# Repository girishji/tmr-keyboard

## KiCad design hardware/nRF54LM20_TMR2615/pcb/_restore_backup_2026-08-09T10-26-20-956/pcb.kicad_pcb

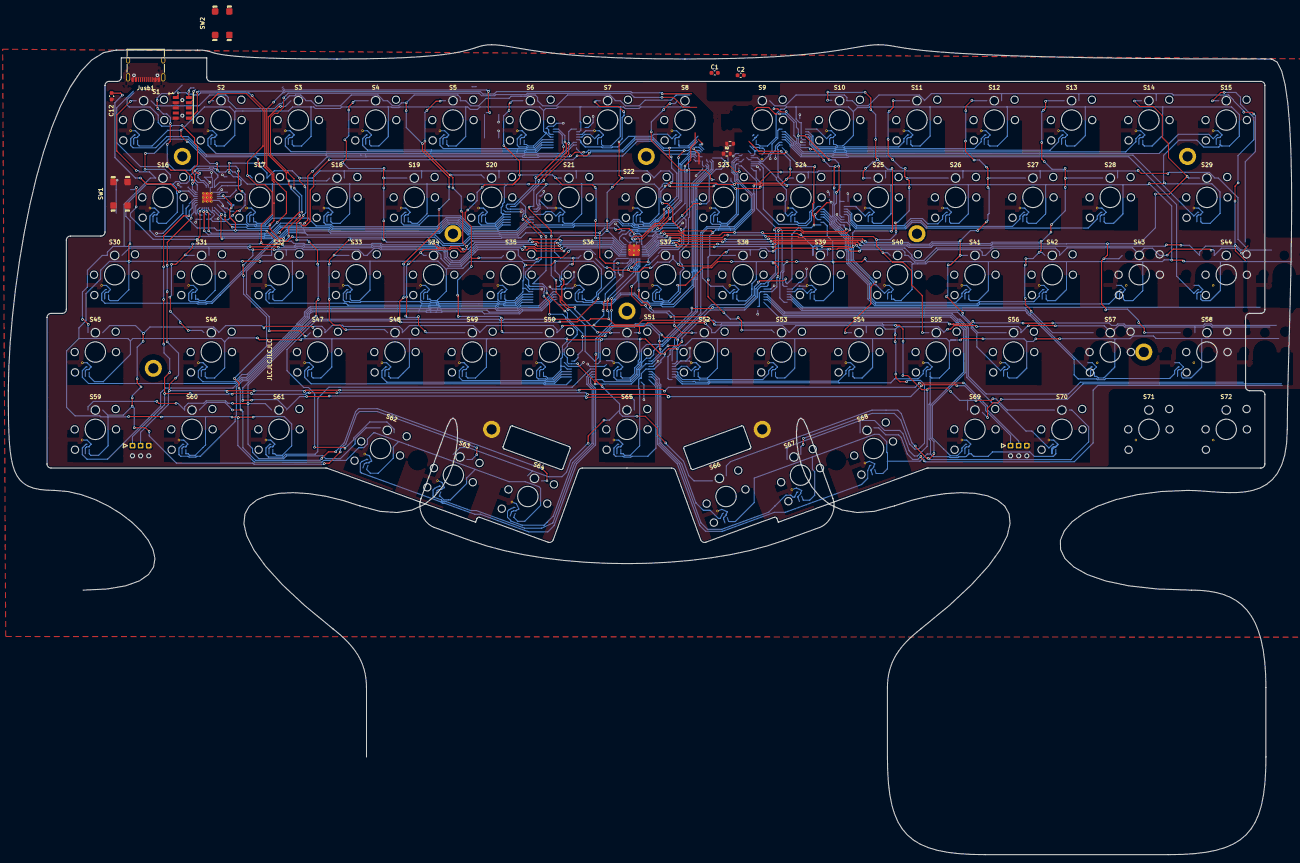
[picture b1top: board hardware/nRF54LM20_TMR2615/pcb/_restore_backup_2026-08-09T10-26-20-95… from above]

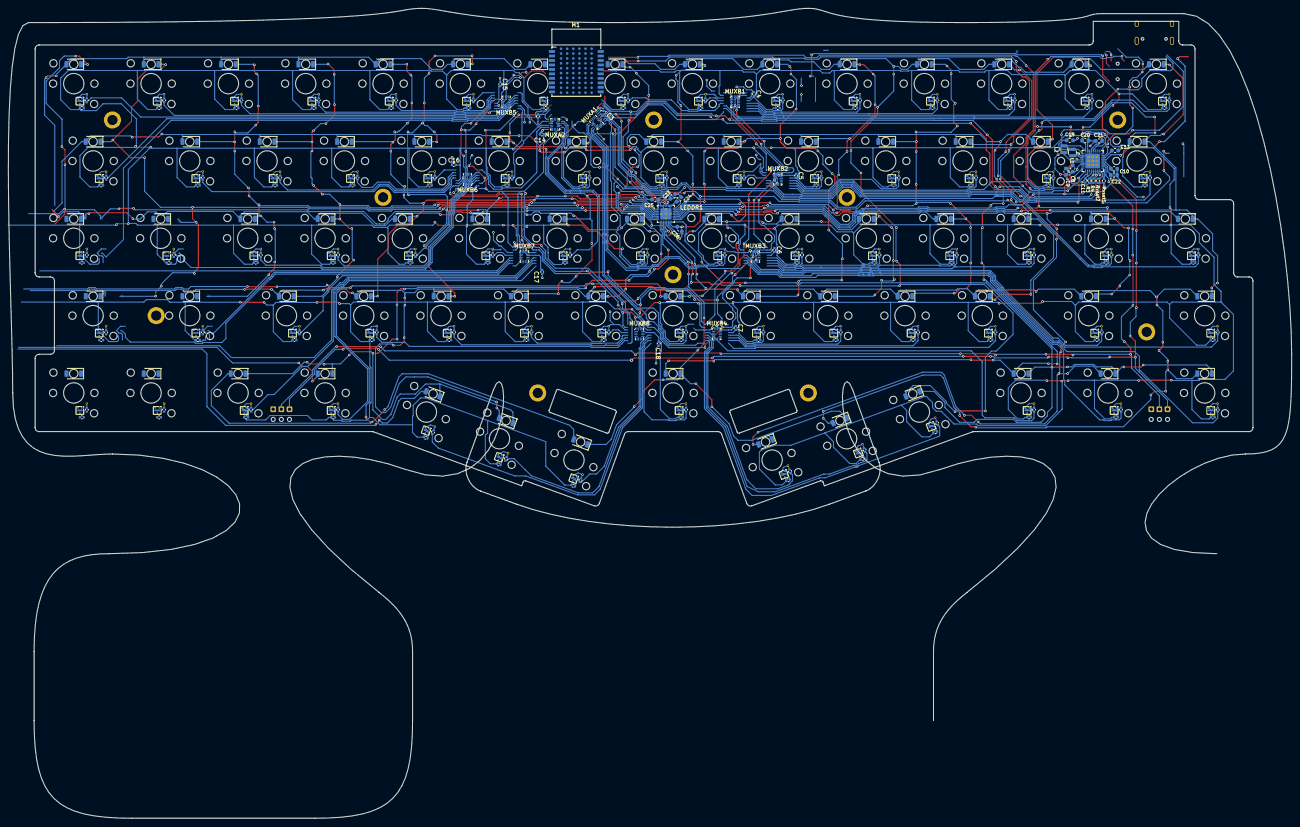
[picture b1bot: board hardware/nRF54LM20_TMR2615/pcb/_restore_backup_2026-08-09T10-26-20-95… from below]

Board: 2 copper layers, 315.3 x 199.0 mm, 426 parts (330 on the bottom side), 144 nets.

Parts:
BAT1, BAT2: PCB_Wire_Solder_3p_Connector
C1, C2, C8, C9, C10, C19, C20: 10uF; C_0603_1608Metric
C3, C4, C5, C6, C7, C14, C15, C16, C17, C18: .1uF; C_0402_1005Metric
C11: 0.1uF; C_0402_1005Metric
C12, C13, C24, C25, C26: 1uF; C_0603_1608Metric
C21, C22: 2.2uF; C_0603_1608Metric
C23: 1nF; C_0603_1608Metric
Cvcc1, Cvcc2, Cvcc3, Cvcc4, Cvcc5, Cvcc6, Cvcc7, Cvcc8, Cvcc9, Cvcc10, Cvcc11, Cvcc12, Cvcc13, Cvcc14, Cvcc15, Cvcc16, Cvcc17, Cvcc18, Cvcc19, Cvcc20, Cvcc21, Cvcc22, Cvcc23, Cvcc24, Cvcc25, Cvcc26, Cvcc27, Cvcc28, Cvcc29, Cvcc30, Cvcc31, Cvcc32, Cvcc33, Cvcc34, Cvcc35, Cvcc36, Cvcc37, Cvcc38, Cvcc39, Cvcc40, Cvcc41, Cvcc42, Cvcc43, Cvcc44, Cvcc45, Cvcc46, Cvcc47, Cvcc48, Cvcc49, Cvcc50, Cvcc51, Cvcc52, Cvcc53, Cvcc54, Cvcc55, Cvcc56, Cvcc57, Cvcc58, Cvcc59, Cvcc60, Cvcc61, Cvcc62, Cvcc63, Cvcc64, Cvcc65, Cvcc66, Cvcc67, Cvcc68, Cvcc69, Cvcc70, Cvcc71, Cvcc72: 0.1uF; C_0402_1005Metric_Cvcc
Cvout1, Cvout2, Cvout3, Cvout4, Cvout5, Cvout6, Cvout7, Cvout8, Cvout9, Cvout10, Cvout11, Cvout12, Cvout13, Cvout14, Cvout15, Cvout16, Cvout17, Cvout18, Cvout19, Cvout20, Cvout21, Cvout22, Cvout23, Cvout24, Cvout25, Cvout26, Cvout27, Cvout28, Cvout29, Cvout30, Cvout31, Cvout32, Cvout33, Cvout34, Cvout35, Cvout36, Cvout37, Cvout38, Cvout39, Cvout40, Cvout41, Cvout42, Cvout43, Cvout44, Cvout45, Cvout46, Cvout47, Cvout48, Cvout49, Cvout50, Cvout51, Cvout52, Cvout53, Cvout54, Cvout55, Cvout56, Cvout57, Cvout58, Cvout59, Cvout60, Cvout61, Cvout62, Cvout63, Cvout64, Cvout65, Cvout66, Cvout67, Cvout68, Cvout69, Cvout70, Cvout71, Cvout72: 0.1nF; C_0402_1005Metric_Cvout
D1, D2, D3, D4, D5, D6, D7, D8, D9, D10, D11, D12, D13, D14, D15, D16, D17, D18, D19, D20, D21, D22, D23, D24, D25, D26, D27, D28, D29, D30, D31, D32, D33, D34, D35, D36, D37, D38, D39, D40, D41, D42, D43, D44, D45, D46, D47, D48, D49, D50, D51, D52, D53, D54, D55, D56, D57, D58, D59, D60, D61, D62, D63, D64, D65, D66, D67, D68, D69, D70, D71, D72: Green LED; LED_1206_3216Metric_ReverseMount_Hole2.1mm
Hs1, Hs2, Hs3, Hs4, Hs5, Hs6, Hs7, Hs8, Hs9, Hs10: SMTSO1.6; SMTSO_M1.6
JLC1: JLC_Order_Num
JTAG1: Conn_ARM_JTAG_SWD_10; SAMTEC-CLP-105-02-X-D-A
Jusb1: USB_TYPE_C_Receptacle_16P; USB_C_Receptacle_XKB_U262-16XN-4BVC11
L1, L2: 2.2uH; L_Samsung_CIGT201610EH2R2MNE
LEDDR1: LP5864; LP5864-VQFN-32-1EP_4x4mm_P0.4mm_EP2.8x2.8mm_ThermalVias
M1: Minew_ME54BS13_V1.0; Minew_ME54BS13
MUXA1, MUXA2: TMUX1574RSV; UQFN-16_1.8x2.6mm_P0.4mm
MUXB1, MUXB2, MUXB3, MUXB4, MUXB5, MUXB6, MUXB7, MUXB8: TMUX1208RSV; UQFN-16_1.8x2.6mm_P0.4mm
PMIC1: nPM1300-QEXX; QFN-32-1EP_5x5mm_P0.5mm_EP3.6x3.6mm_ThermalVias
R1, R2: 27R; R_0603_1608Metric
R3, R4: 10k; R_0402_1005Metric
Rvset1: 150k; R_0402_1005Metric
Rvset2: 4.7k; R_0402_1005Metric
S1, S2, S3, S4, S5, S6, S7, S8, S9, S10, S11, S12, S13, S14, S15, S16, S17, S18, S19, S20, S21, S22, S23, S24, S25, S26, S27, S28, S29, S30, S31, S32, S33, S34, S35, S36, S37, S38, S39, S40, S41, S42, S43, S44, S45, S46, S47, S48, S49, S50, S51, S52, S53, S54, S55, S56, S57, S58, S59, S60, S61, S62, S63, S64, S65, S66, S67, S68, S69, S70, S71, S72: Switch; Kailh_gateron_sw_lowpro
SW1, SW2: SW_DIP_x01; Aliexpress_SW_TACT_4x4x1.5mm
Stb1, Stb2: TMR_switch_stab_2.0u; Stabilizer_Lowpro_2U
TMR1, TMR2, TMR3, TMR4, TMR5, TMR6, TMR7, TMR8, TMR9, TMR10, TMR11, TMR12, TMR13, TMR14, TMR15, TMR16, TMR17, TMR18, TMR19, TMR20, TMR21, TMR22, TMR23, TMR24, TMR25, TMR26, TMR27, TMR28, TMR29, TMR30, TMR31, TMR32, TMR33, TMR34, TMR35, TMR36, TMR37, TMR38, TMR39, TMR40, TMR41, TMR42, TMR43, TMR44, TMR45, TMR46, TMR47, TMR48, TMR49, TMR50, TMR51, TMR52, TMR53, TMR54, TMR55, TMR56, TMR57, TMR58, TMR59, TMR60, TMR61, TMR62, TMR63, TMR64, TMR65, TMR66, TMR67, TMR68, TMR69, TMR70, TMR71, TMR72: TMR2615; TMR2615-DFN-3L-1.6x1.6

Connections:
/AIN0: M1.A7 (P1.00/AIN0), MUXA1.2 (D1)
/AIN1: M1.B7 (P1.31/AIN1), MUXA1.5 (D2)
/AIN2: M1.A9 (P1.30/AIN2), MUXA1.7 (D3)
/AIN3: M1.B9 (P1.29/AIN3), MUXA1.10 (D4)
/AIN4: M1.A6 (P1.06/AIN4), MUXA2.7 (D3)
/AIN5: M1.C7 (P1.05/AIN5), MUXA2.10 (D4)
/AIN6: M1.A8 (P1.04/AIN6), MUXA2.2 (D1)
/AIN7: M1.B8 (P1.03/AIN7), MUXA2.5 (D2)
/ANA_01: Cvout1.1, MUXB1.5 (S4), TMR1.1 (V_{OUT})
/ANA_02: Cvout2.1, MUXB1.4 (S3), TMR2.1 (V_{OUT})
/ANA_03: Cvout3.1, MUXB1.7 (S8), TMR3.1 (V_{OUT})
/ANA_04: Cvout4.1, MUXB1.8 (S7), TMR4.1 (V_{OUT})
/ANA_05: Cvout5.1, MUXB1.9 (S6), TMR5.1 (V_{OUT})
/ANA_06: Cvout6.1, MUXB1.10 (S5), TMR6.1 (V_{OUT})
/ANA_07: Cvout7.1, MUXB1.2 (S1), TMR7.1 (V_{OUT})
/ANA_08: Cvout8.1, MUXB1.3 (S2), TMR8.1 (V_{OUT})
/ANA_09: Cvout9.1, MUXA2.8 (S3B), TMR9.1 (V_{OUT})
/ANA_10: Cvout10.1, MUXB5.7 (S8), TMR10.1 (V_{OUT})
/ANA_11: Cvout11.1, MUXB5.8 (S7), TMR11.1 (V_{OUT})
/ANA_12: Cvout12.1, MUXB5.9 (S6), TMR12.1 (V_{OUT})
/ANA_13: Cvout13.1, MUXB5.10 (S5), TMR13.1 (V_{OUT})
/ANA_14: Cvout14.1, MUXB5.5 (S4), TMR14.1 (V_{OUT})
/ANA_15: Cvout15.1, MUXB5.4 (S3), TMR15.1 (V_{OUT})
/ANA_16: Cvout16.1, MUXB2.3 (S2), TMR16.1 (V_{OUT})
/ANA_17: Cvout17.1, MUXB2.7 (S8), TMR17.1 (V_{OUT})
/ANA_18: Cvout18.1, MUXB2.8 (S7), TMR18.1 (V_{OUT})
/ANA_19: Cvout19.1, MUXB2.9 (S6), TMR19.1 (V_{OUT})
/ANA_20: Cvout20.1, MUXB2.10 (S5), TMR20.1 (V_{OUT})
/ANA_21: Cvout21.1, MUXB2.2 (S1), TMR21.1 (V_{OUT})
/ANA_22: Cvout22.1, MUXA1.11 (S4B), TMR22.1 (V_{OUT})
/ANA_23: Cvout23.1, MUXA2.4 (S2B), TMR23.1 (V_{OUT})
/ANA_24: Cvout24.1, MUXA2.11 (S4B), TMR24.1 (V_{OUT})
/ANA_25: Cvout25.1, MUXB6.7 (S8), TMR25.1 (V_{OUT})
/ANA_26: Cvout26.1, MUXB6.8 (S7), TMR26.1 (V_{OUT})
/ANA_27: Cvout27.1, MUXB6.9 (S6), TMR27.1 (V_{OUT})
/ANA_28: Cvout28.1, MUXB6.10 (S5), TMR28.1 (V_{OUT})
/ANA_29: Cvout29.1, MUXB5.3 (S2), TMR29.1 (V_{OUT})
/ANA_30: Cvout30.1, MUXB2.5 (S4), TMR30.1 (V_{OUT})
/ANA_31: Cvout31.1, MUXB2.4 (S3), TMR31.1 (V_{OUT})
/ANA_32: Cvout32.1, MUXB3.7 (S8), TMR32.1 (V_{OUT})
/ANA_33: Cvout33.1, MUXB3.8 (S7), TMR33.1 (V_{OUT})
/ANA_34: Cvout34.1, MUXB3.9 (S6), TMR34.1 (V_{OUT})
/ANA_35: Cvout35.1, MUXB3.10 (S5), TMR35.1 (V_{OUT})
/ANA_36: Cvout36.1, MUXA1.4 (S2B), TMR36.1 (V_{OUT})
/ANA_37: Cvout37.1, MUXA1.8 (S3B), TMR37.1 (V_{OUT})
/ANA_38: Cvout38.1, MUXA2.1 (S1B), TMR38.1 (V_{OUT})
/ANA_39: Cvout39.1, MUXB7.2 (S1), TMR39.1 (V_{OUT})
/ANA_40: Cvout40.1, MUXB6.5 (S4), TMR40.1 (V_{OUT})
/ANA_41: Cvout41.1, MUXB6.4 (S3), TMR41.1 (V_{OUT})
/ANA_42: Cvout42.1, MUXB6.3 (S2), TMR42.1 (V_{OUT})
/ANA_43: Cvout43.1, MUXB6.2 (S1), TMR43.1 (V_{OUT})
/ANA_44: Cvout44.1, MUXB5.2 (S1), TMR44.1 (V_{OUT})
/ANA_45: Cvout45.1, MUXB3.3 (S2), TMR45.1 (V_{OUT})
/ANA_46: Cvout46.1, MUXB3.2 (S1), TMR46.1 (V_{OUT})
/ANA_47: Cvout47.1, MUXB4.7 (S8), TMR47.1 (V_{OUT})
/ANA_48: Cvout48.1, MUXB4.8 (S7), TMR48.1 (V_{OUT})
/ANA_49: Cvout49.1, MUXB4.9 (S6), TMR49.1 (V_{OUT})
/ANA_50: Cvout50.1, MUXB4.10 (S5), TMR50.1 (V_{OUT})
/ANA_51: Cvout51.1, MUXA1.1 (S1B), TMR51.1 (V_{OUT})
/ANA_52: Cvout52.1, MUXB8.2 (S1), TMR52.1 (V_{OUT})
/ANA_53: Cvout53.1, MUXB8.3 (S2), TMR53.1 (V_{OUT})
/ANA_54: Cvout54.1, MUXB8.4 (S3), TMR54.1 (V_{OUT})
/ANA_55: Cvout55.1, MUXB8.5 (S4), TMR55.1 (V_{OUT})
/ANA_56: Cvout56.1, MUXB7.10 (S5), TMR56.1 (V_{OUT})
/ANA_57: Cvout57.1, MUXB7.4 (S3), TMR57.1 (V_{OUT})
/ANA_58: Cvout58.1, MUXB7.5 (S4), TMR58.1 (V_{OUT})
/ANA_59: Cvout59.1, MUXB3.4 (S3), TMR59.1 (V_{OUT})
/ANA_60: Cvout60.1, MUXB3.5 (S4), TMR60.1 (V_{OUT})
/ANA_61: Cvout61.1, MUXB4.2 (S1), TMR61.1 (V_{OUT})
/ANA_62: Cvout62.1, MUXB4.5 (S4), TMR62.1 (V_{OUT})
/ANA_63: Cvout63.1, MUXB4.4 (S3), TMR63.1 (V_{OUT})
/ANA_64: Cvout64.1, MUXB4.3 (S2), TMR64.1 (V_{OUT})
/ANA_65: Cvout65.1, MUXB8.7 (S8), TMR65.1 (V_{OUT})
/ANA_66: Cvout66.1, MUXB8.10 (S5), TMR66.1 (V_{OUT})
/ANA_67: Cvout67.1, MUXB8.9 (S6), TMR67.1 (V_{OUT})
/ANA_68: Cvout68.1, MUXB8.8 (S7), TMR68.1 (V_{OUT})
/ANA_69: Cvout69.1, MUXB7.7 (S8), TMR69.1 (V_{OUT})
/ANA_70: Cvout70.1, MUXB7.8 (S7), TMR70.1 (V_{OUT})
/ANA_71: Cvout71.1, MUXB7.9 (S6), TMR71.1 (V_{OUT})
/ANA_72: Cvout72.1, MUXB7.3 (S2), TMR72.1 (V_{OUT})
/CS0: D9.1 (K), D24.1 (K), D38.1 (K), D53.1 (K), LEDDR1.2 (CS0)
/CS1: D10.1 (K), D25.1 (K), D39.1 (K), D54.1 (K), LEDDR1.3 (CS1)
/CS2: D11.1 (K), D26.1 (K), D40.1 (K), D55.1 (K), LEDDR1.4 (CS2)
/CS3: D12.1 (K), D27.1 (K), D41.1 (K), D56.1 (K), LEDDR1.5 (CS3)
/CS4: D13.1 (K), D28.1 (K), D42.1 (K), D57.1 (K), LEDDR1.6 (CS4)
/CS5: D14.1 (K), D29.1 (K), D43.1 (K), D58.1 (K), LEDDR1.7 (CS5)
/CS6: D15.1 (K), D44.1 (K), D71.1 (K), D72.1 (K), LEDDR1.8 (CS6)
/CS7: D67.1 (K), D68.1 (K), D69.1 (K), D70.1 (K), LEDDR1.9 (CS7)
/CS8: D63.1 (K), D64.1 (K), D65.1 (K), D66.1 (K), LEDDR1.10 (CS8)
/CS9: D59.1 (K), D60.1 (K), D61.1 (K), D62.1 (K), LEDDR1.16 (CS9)
/CS10: D1.1 (K), D16.1 (K), D30.1 (K), D45.1 (K), LEDDR1.17 (CS10)
/CS11: D2.1 (K), D17.1 (K), D31.1 (K), D46.1 (K), LEDDR1.18 (CS11)
/CS12: D3.1 (K), D18.1 (K), D32.1 (K), D47.1 (K), LEDDR1.19 (CS12)
/CS13: D4.1 (K), D19.1 (K), D33.1 (K), D48.1 (K), LEDDR1.20 (CS13)
/CS14: D5.1 (K), D20.1 (K), D34.1 (K), D49.1 (K), LEDDR1.21 (CS14)
/CS15: D6.1 (K), D21.1 (K), D35.1 (K), D50.1 (K), LEDDR1.22 (CS15)
/CS16: D7.1 (K), D22.1 (K), D36.1 (K), D51.1 (K), LEDDR1.23 (CS16)
/CS17: D8.1 (K), D23.1 (K), D37.1 (K), D52.1 (K), LEDDR1.24 (CS17)
/GPIO_X: M1.13 (P1.23), PMIC1.10 (GPIO3)
/INT: M1.12 (P1.26), PMIC1.8 (GPIO1)
/LED_DR_EN: C23.1, LEDDR1.32 (VIO_EN), M1.F3 (P1.13)
/LOADSW_CTRL: M1.14 (P1.19), PMIC1.9 (GPIO2)
/MUXA_SEL: M1.15 (P1.18), MUXA1.15 (SEL), MUXA2.15 (SEL)
/MUXB_SEL_0: M1.17 (P1.16), MUXB1.15 (A0), MUXB2.15 (A0), MUXB3.15 (A0), MUXB4.15 (A0), MUXB5.15 (A0), MUXB6.15 (A0), MUXB7.15 (A0), MUXB8.15 (A0)
/MUXB_SEL_1: M1.16 (P1.17), MUXB1.14 (A1), MUXB2.14 (A1), MUXB3.14 (A1), MUXB4.14 (A1), MUXB5.14 (A1), MUXB6.14 (A1), MUXB7.14 (A1), MUXB8.14 (A1)
/MUXB_SEL_2: M1.18 (P1.15), MUXB1.13 (A2), MUXB2.13 (A2), MUXB3.13 (A2), MUXB4.13 (A2), MUXB5.13 (A2), MUXB6.13 (A2), MUXB7.13 (A2), MUXB8.13 (A2)
/MUX_B_1: MUXA1.12 (S4A), MUXB1.6 (D)
/MUX_B_2: MUXA1.9 (S3A), MUXB2.6 (D)
/MUX_B_3: MUXA1.3 (S2A), MUXB3.6 (D)
/MUX_B_4: MUXA1.16 (S1A), MUXB4.6 (D)
/MUX_B_5: MUXA2.9 (S3A), MUXB5.6 (D)
/MUX_B_6: MUXA2.12 (S4A), MUXB6.6 (D)
/MUX_B_7: MUXA2.16 (S1A), MUXB7.6 (D)
/MUX_B_8: MUXA2.3 (S2A), MUXB8.6 (D)
/NRESET: JTAG1.10 (~RESET), M1.4 (nRESET), SW1.2
/SCL: LEDDR1.28 (SCL_SCLK), M1.F4 (P1.12), PMIC1.14 (SCL), R3.2
/SDA: LEDDR1.29 (SDA_MOSI), M1.F5 (P1.11), PMIC1.13 (SDA), R4.2
/SW0: D1.2 (A), D2.2 (A), D3.2 (A), D4.2 (A), D5.2 (A), D6.2 (A), D7.2 (A), D8.2 (A), D9.2 (A), D10.2 (A), D11.2 (A), D12.2 (A), D13.2 (A), D14.2 (A), D15.2 (A), D62.2 (A), D66.2 (A), D70.2 (A), LEDDR1.11 (SW0)
/SW1: D16.2 (A), D17.2 (A), D18.2 (A), D19.2 (A), D20.2 (A), D21.2 (A), D22.2 (A), D23.2 (A), D24.2 (A), D25.2 (A), D26.2 (A), D27.2 (A), D28.2 (A), D29.2 (A), D61.2 (A), D65.2 (A), D69.2 (A), D72.2 (A), LEDDR1.12 (SW1)
/SW2: D30.2 (A), D31.2 (A), D32.2 (A), D33.2 (A), D34.2 (A), D35.2 (A), D36.2 (A), D37.2 (A), D38.2 (A), D39.2 (A), D40.2 (A), D41.2 (A), D42.2 (A), D43.2 (A), D44.2 (A), D60.2 (A), D64.2 (A), D68.2 (A), LEDDR1.13 (SW2)
/SW3: D45.2 (A), D46.2 (A), D47.2 (A), D48.2 (A), D49.2 (A), D50.2 (A), D51.2 (A), D52.2 (A), D53.2 (A), D54.2 (A), D55.2 (A), D56.2 (A), D57.2 (A), D58.2 (A), D59.2 (A), D63.2 (A), D67.2 (A), D71.2 (A), LEDDR1.14 (SW3)
/SWDCLK: JTAG1.4 (SWCLK/TCK), M1.6 (SWDCLK)
/SWDIO: JTAG1.2 (SWDIO/TMS), M1.5 (SWDIO)
/USB_D+: Jusb1.A6 (D1+), Jusb1.B6 (D2+), R2.1
/USB_D-: Jusb1.A7 (D1-), Jusb1.B7 (D2-), R1.1
/VBAT: BAT1.1 (VBAT), BAT2.1 (VBAT), C22.1, PMIC1.19 (VBAT)
/VBUSOUT: C2.1, C13.1, M1.9 (VBUS), PMIC1.22 (VBUSOUT)
/VDD_nRF: C1.1, C11.2, C19.1, JTAG1.1 (VTref), L1.1, M1.19 (VCC), PMIC1.1 (VOUT1), PMIC1.12 (VDDIO), R3.1, R4.1
/VOUT2: C20.1, L2.1, PMIC1.28 (LSIN1/VINLDO1), PMIC1.32 (VOUT2)
/VSYS: C8.1, C9.1, C10.1, C25.1, C26.1, LEDDR1.1 (VCC), LEDDR1.15 (VLED), PMIC1.4 (PVDD), PMIC1.20 (VSYS)
GND: BAT1.3 (GND), BAT2.3 (GND), C1.2, C2.2, C3.1, C4.1, C5.1, C6.1, C7.1, C8.2, C9.2, C10.2, C11.1, C12.2, C13.2, C14.1, C15.1, C16.1, C17.1, C18.1, C19.2, C20.2, C21.2, C22.2, C23.2, C24.1, C25.2, C26.2, Cvcc1.2, Cvcc2.2, Cvcc3.2, Cvcc4.2, Cvcc5.2, Cvcc6.2, Cvcc7.2, Cvcc8.2, Cvcc9.2, Cvcc10.2, Cvcc11.2, Cvcc12.2, Cvcc13.2, Cvcc14.2, Cvcc15.2, Cvcc16.2, Cvcc17.2, Cvcc18.2, Cvcc19.2, Cvcc20.2, Cvcc21.2, Cvcc22.2, Cvcc23.2, Cvcc24.2, Cvcc25.2, Cvcc26.2, Cvcc27.2, Cvcc28.2, Cvcc29.2, Cvcc30.2, Cvcc31.2, Cvcc32.2, Cvcc33.2, Cvcc34.2, Cvcc35.2, Cvcc36.2, Cvcc37.2, Cvcc38.2, Cvcc39.2, Cvcc40.2, Cvcc41.2, Cvcc42.2, Cvcc43.2, Cvcc44.2, Cvcc45.2, Cvcc46.2, Cvcc47.2, Cvcc48.2, Cvcc49.2, Cvcc50.2, Cvcc51.2, Cvcc52.2, Cvcc53.2, Cvcc54.2, Cvcc55.2, Cvcc56.2, Cvcc57.2, Cvcc58.2, Cvcc59.2, Cvcc60.2, Cvcc61.2, Cvcc62.2, Cvcc63.2, Cvcc64.2, Cvcc65.2, Cvcc66.2, Cvcc67.2, Cvcc68.2, Cvcc69.2, Cvcc70.2, Cvcc71.2, Cvcc72.2, Cvout1.2, Cvout2.2, Cvout3.2, Cvout4.2, Cvout5.2, Cvout6.2, Cvout7.2, Cvout8.2, Cvout9.2, Cvout10.2, Cvout11.2, Cvout12.2, Cvout13.2, Cvout14.2, Cvout15.2, Cvout16.2, Cvout17.2, Cvout18.2, Cvout19.2, Cvout20.2, Cvout21.2, Cvout22.2, Cvout23.2, Cvout24.2, Cvout25.2, Cvout26.2, Cvout27.2, Cvout28.2, Cvout29.2, Cvout30.2, Cvout31.2, Cvout32.2, Cvout33.2, Cvout34.2, Cvout35.2, Cvout36.2, Cvout37.2, Cvout38.2, Cvout39.2, Cvout40.2, Cvout41.2, Cvout42.2, Cvout43.2, Cvout44.2, Cvout45.2, Cvout46.2, Cvout47.2, Cvout48.2, Cvout49.2, Cvout50.2, Cvout51.2, Cvout52.2, Cvout53.2, Cvout54.2, Cvout55.2, Cvout56.2, Cvout57.2, Cvout58.2, Cvout59.2, Cvout60.2, Cvout61.2, Cvout62.2, Cvout63.2, Cvout64.2, Cvout65.2, Cvout66.2, Cvout67.2, Cvout68.2, Cvout69.2, Cvout70.2, Cvout71.2, Cvout72.2, JTAG1.3 (GND), JTAG1.5 (GND), JTAG1.9 (GNDDetect), Jusb1.A1 (GND), Jusb1.A12 (GND), Jusb1.B1 (GND), Jusb1.B12 (GND), Jusb1.SH (SHIELD), LEDDR1.26 (IFS), LEDDR1.27 (VSYNC), LEDDR1.30 (ADDR0_MISO), LEDDR1.31 (ADDR1_SS), LEDDR1.33 (GND), M1.1 (GND), M1.3 (GND), M1.10 (GND), M1.11 (GND), M1.20 (GND), M1.D0 (GND), M1.E0 (GND), M1.F0 (GND), MUXA1.6 (GND), MUXA1.13 (~EN), MUXA2.6 (GND), MUXA2.13 (~EN), MUXB1.12 (GND), MUXB2.12 (GND), MUXB3.12 (GND), MUXB4.12 (GND), MUXB5.12 (GND), MUXB6.12 (GND), MUXB7.12 (GND), MUXB8.12 (GND), PMIC1.2 (PVSS1), PMIC1.6 (PVSS2), PMIC1.30 (LSIN2/VINLDO2), PMIC1.31 (LSOUT2/VOUTLDO2), PMIC1.33 (AVSS), Rvset1.1, Rvset2.1, SW1.1, SW2.1, TMR1.2 (GND), TMR1.4 (GND), TMR2.2 (GND), TMR2.4 (GND), TMR3.2 (GND), TMR3.4 (GND), TMR4.2 (GND), TMR4.4 (GND), TMR5.2 (GND), TMR5.4 (GND), TMR6.2 (GND), TMR6.4 (GND), TMR7.2 (GND), TMR7.4 (GND), TMR8.2 (GND), TMR8.4 (GND), TMR9.2 (GND), TMR9.4 (GND), TMR10.2 (GND), TMR10.4 (GND), TMR11.2 (GND), TMR11.4 (GND), TMR12.2 (GND), TMR12.4 (GND), TMR13.2 (GND), TMR13.4 (GND), TMR14.2 (GND), TMR14.4 (GND), TMR15.2 (GND), TMR15.4 (GND), TMR16.2 (GND), TMR16.4 (GND), TMR17.2 (GND), TMR17.4 (GND), TMR18.2 (GND), TMR18.4 (GND), TMR19.2 (GND), TMR19.4 (GND), TMR20.2 (GND), TMR20.4 (GND), TMR21.2 (GND), TMR21.4 (GND), TMR22.2 (GND), TMR22.4 (GND), TMR23.2 (GND), TMR23.4 (GND), TMR24.2 (GND), TMR24.4 (GND), TMR25.2 (GND), TMR25.4 (GND), TMR26.2 (GND), TMR26.4 (GND), TMR27.2 (GND), TMR27.4 (GND), TMR28.2 (GND), TMR28.4 (GND), TMR29.2 (GND), TMR29.4 (GND), TMR30.2 (GND), TMR30.4 (GND), TMR31.2 (GND), TMR31.4 (GND), TMR32.2 (GND), TMR32.4 (GND), TMR33.2 (GND), TMR33.4 (GND), TMR34.2 (GND), TMR34.4 (GND), TMR35.2 (GND), TMR35.4 (GND), TMR36.2 (GND), TMR36.4 (GND), TMR37.2 (GND), TMR37.4 (GND), TMR38.2 (GND), TMR38.4 (GND), TMR39.2 (GND), TMR39.4 (GND), TMR40.2 (GND), TMR40.4 (GND), TMR41.2 (GND), TMR41.4 (GND), TMR42.2 (GND), TMR42.4 (GND), TMR43.2 (GND), TMR43.4 (GND), TMR44.2 (GND), TMR44.4 (GND), TMR45.2 (GND), TMR45.4 (GND), TMR46.2 (GND), TMR46.4 (GND), TMR47.2 (GND), TMR47.4 (GND), TMR48.2 (GND), TMR48.4 (GND), TMR49.2 (GND), TMR49.4 (GND), TMR50.2 (GND), TMR50.4 (GND), TMR51.2 (GND), TMR51.4 (GND), TMR52.2 (GND), TMR52.4 (GND), TMR53.2 (GND), TMR53.4 (GND), TMR54.2 (GND), TMR54.4 (GND), TMR55.2 (GND), TMR55.4 (GND), TMR56.2 (GND), TMR56.4 (GND), TMR57.2 (GND), TMR57.4 (GND), TMR58.2 (GND), TMR58.4 (GND), TMR59.2 (GND), TMR59.4 (GND), TMR60.2 (GND), TMR60.4 (GND), TMR61.2 (GND), TMR61.4 (GND), TMR62.2 (GND), TMR62.4 (GND), TMR63.2 (GND), TMR63.4 (GND), TMR64.2 (GND), TMR64.4 (GND), TMR65.2 (GND), TMR65.4 (GND), TMR66.2 (GND), TMR66.4 (GND), TMR67.2 (GND), TMR67.4 (GND), TMR68.2 (GND), TMR68.4 (GND), TMR69.2 (GND), TMR69.4 (GND), TMR70.2 (GND), TMR70.4 (GND), TMR71.2 (GND), TMR71.4 (GND), TMR72.2 (GND), TMR72.4 (GND)
unnamed: BAT1.2 (NTC), BAT2.2 (NTC), PMIC1.18 (NTC)
unnamed: Jusb1.A5 (CC1), PMIC1.23 (CC1)
unnamed: Jusb1.B5 (CC2), PMIC1.24 (CC2)
unnamed: C24.2, LEDDR1.25 (VCAP)
unnamed: M1.8 (D+), R2.2
unnamed: M1.7 (D-), R1.2
unnamed: PMIC1.15 (SHPHLD), SW2.2
unnamed: L1.2, PMIC1.3 (SW1)
unnamed: L2.2, PMIC1.5 (SW2)
unnamed: C12.1, Jusb1.A4 (VBUS), Jusb1.A9 (VBUS), Jusb1.B4 (VBUS), Jusb1.B9 (VBUS), PMIC1.21 (VBUS)
unnamed: PMIC1.17 (VSET1), Rvset1.2
unnamed: PMIC1.16 (VSET2), Rvset2.2
VCCS: C3.2, C4.2, C5.2, C6.2, C7.2, C14.2, C15.2, C16.2, C17.2, C18.2, C21.1, Cvcc1.1, Cvcc2.1, Cvcc3.1, Cvcc4.1, Cvcc5.1, Cvcc6.1, Cvcc7.1, Cvcc8.1, Cvcc9.1, Cvcc10.1, Cvcc11.1, Cvcc12.1, Cvcc13.1, Cvcc14.1, Cvcc15.1, Cvcc16.1, Cvcc17.1, Cvcc18.1, Cvcc19.1, Cvcc20.1, Cvcc21.1, Cvcc22.1, Cvcc23.1, Cvcc24.1, Cvcc25.1, Cvcc26.1, Cvcc27.1, Cvcc28.1, Cvcc29.1, Cvcc30.1, Cvcc31.1, Cvcc32.1, Cvcc33.1, Cvcc34.1, Cvcc35.1, Cvcc36.1, Cvcc37.1, Cvcc38.1, Cvcc39.1, Cvcc40.1, Cvcc41.1, Cvcc42.1, Cvcc43.1, Cvcc44.1, Cvcc45.1, Cvcc46.1, Cvcc47.1, Cvcc48.1, Cvcc49.1, Cvcc50.1, Cvcc51.1, Cvcc52.1, Cvcc53.1, Cvcc54.1, Cvcc55.1, Cvcc56.1, Cvcc57.1, Cvcc58.1, Cvcc59.1, Cvcc60.1, Cvcc61.1, Cvcc62.1, Cvcc63.1, Cvcc64.1, Cvcc65.1, Cvcc66.1, Cvcc67.1, Cvcc68.1, Cvcc69.1, Cvcc70.1, Cvcc71.1, Cvcc72.1, MUXA1.14 (VDD), MUXA2.14 (VDD), MUXB1.11 (VDD), MUXB1.16 (EN), MUXB2.11 (VDD), MUXB2.16 (EN), MUXB3.11 (VDD), MUXB3.16 (EN), MUXB4.11 (VDD), MUXB4.16 (EN), MUXB5.11 (VDD), MUXB5.16 (EN), MUXB6.11 (VDD), MUXB6.16 (EN), MUXB7.11 (VDD), MUXB7.16 (EN), MUXB8.11 (VDD), MUXB8.16 (EN), PMIC1.29 (LSOUT1/VOUTLDO1), TMR1.3 (V_{CC}), TMR2.3 (V_{CC}), TMR3.3 (V_{CC}), TMR4.3 (V_{CC}), TMR5.3 (V_{CC}), TMR6.3 (V_{CC}), TMR7.3 (V_{CC}), TMR8.3 (V_{CC}), TMR9.3 (V_{CC}), TMR10.3 (V_{CC}), TMR11.3 (V_{CC}), TMR12.3 (V_{CC}), TMR13.3 (V_{CC}), TMR14.3 (V_{CC}), TMR15.3 (V_{CC}), TMR16.3 (V_{CC}), TMR17.3 (V_{CC}), TMR18.3 (V_{CC}), TMR19.3 (V_{CC}), TMR20.3 (V_{CC}), TMR21.3 (V_{CC}), TMR22.3 (V_{CC}), TMR23.3 (V_{CC}), TMR24.3 (V_{CC}), TMR25.3 (V_{CC}), TMR26.3 (V_{CC}), TMR27.3 (V_{CC}), TMR28.3 (V_{CC}), TMR29.3 (V_{CC}), TMR30.3 (V_{CC}), TMR31.3 (V_{CC}), TMR32.3 (V_{CC}), TMR33.3 (V_{CC}), TMR34.3 (V_{CC}), TMR35.3 (V_{CC}), TMR36.3 (V_{CC}), TMR37.3 (V_{CC}), TMR38.3 (V_{CC}), TMR39.3 (V_{CC}), TMR40.3 (V_{CC}), TMR41.3 (V_{CC}), TMR42.3 (V_{CC}), TMR43.3 (V_{CC}), TMR44.3 (V_{CC}), TMR45.3 (V_{CC}), TMR46.3 (V_{CC}), TMR47.3 (V_{CC}), TMR48.3 (V_{CC}), TMR49.3 (V_{CC}), TMR50.3 (V_{CC}), TMR51.3 (V_{CC}), TMR52.3 (V_{CC}), TMR53.3 (V_{CC}), TMR54.3 (V_{CC}), TMR55.3 (V_{CC}), TMR56.3 (V_{CC}), TMR57.3 (V_{CC}), TMR58.3 (V_{CC}), TMR59.3 (V_{CC}), TMR60.3 (V_{CC}), TMR61.3 (V_{CC}), TMR62.3 (V_{CC}), TMR63.3 (V_{CC}), TMR64.3 (V_{CC}), TMR65.3 (V_{CC}), TMR66.3 (V_{CC}), TMR67.3 (V_{CC}), TMR68.3 (V_{CC}), TMR69.3 (V_{CC}), TMR70.3 (V_{CC}), TMR71.3 (V_{CC}), TMR72.3 (V_{CC})
